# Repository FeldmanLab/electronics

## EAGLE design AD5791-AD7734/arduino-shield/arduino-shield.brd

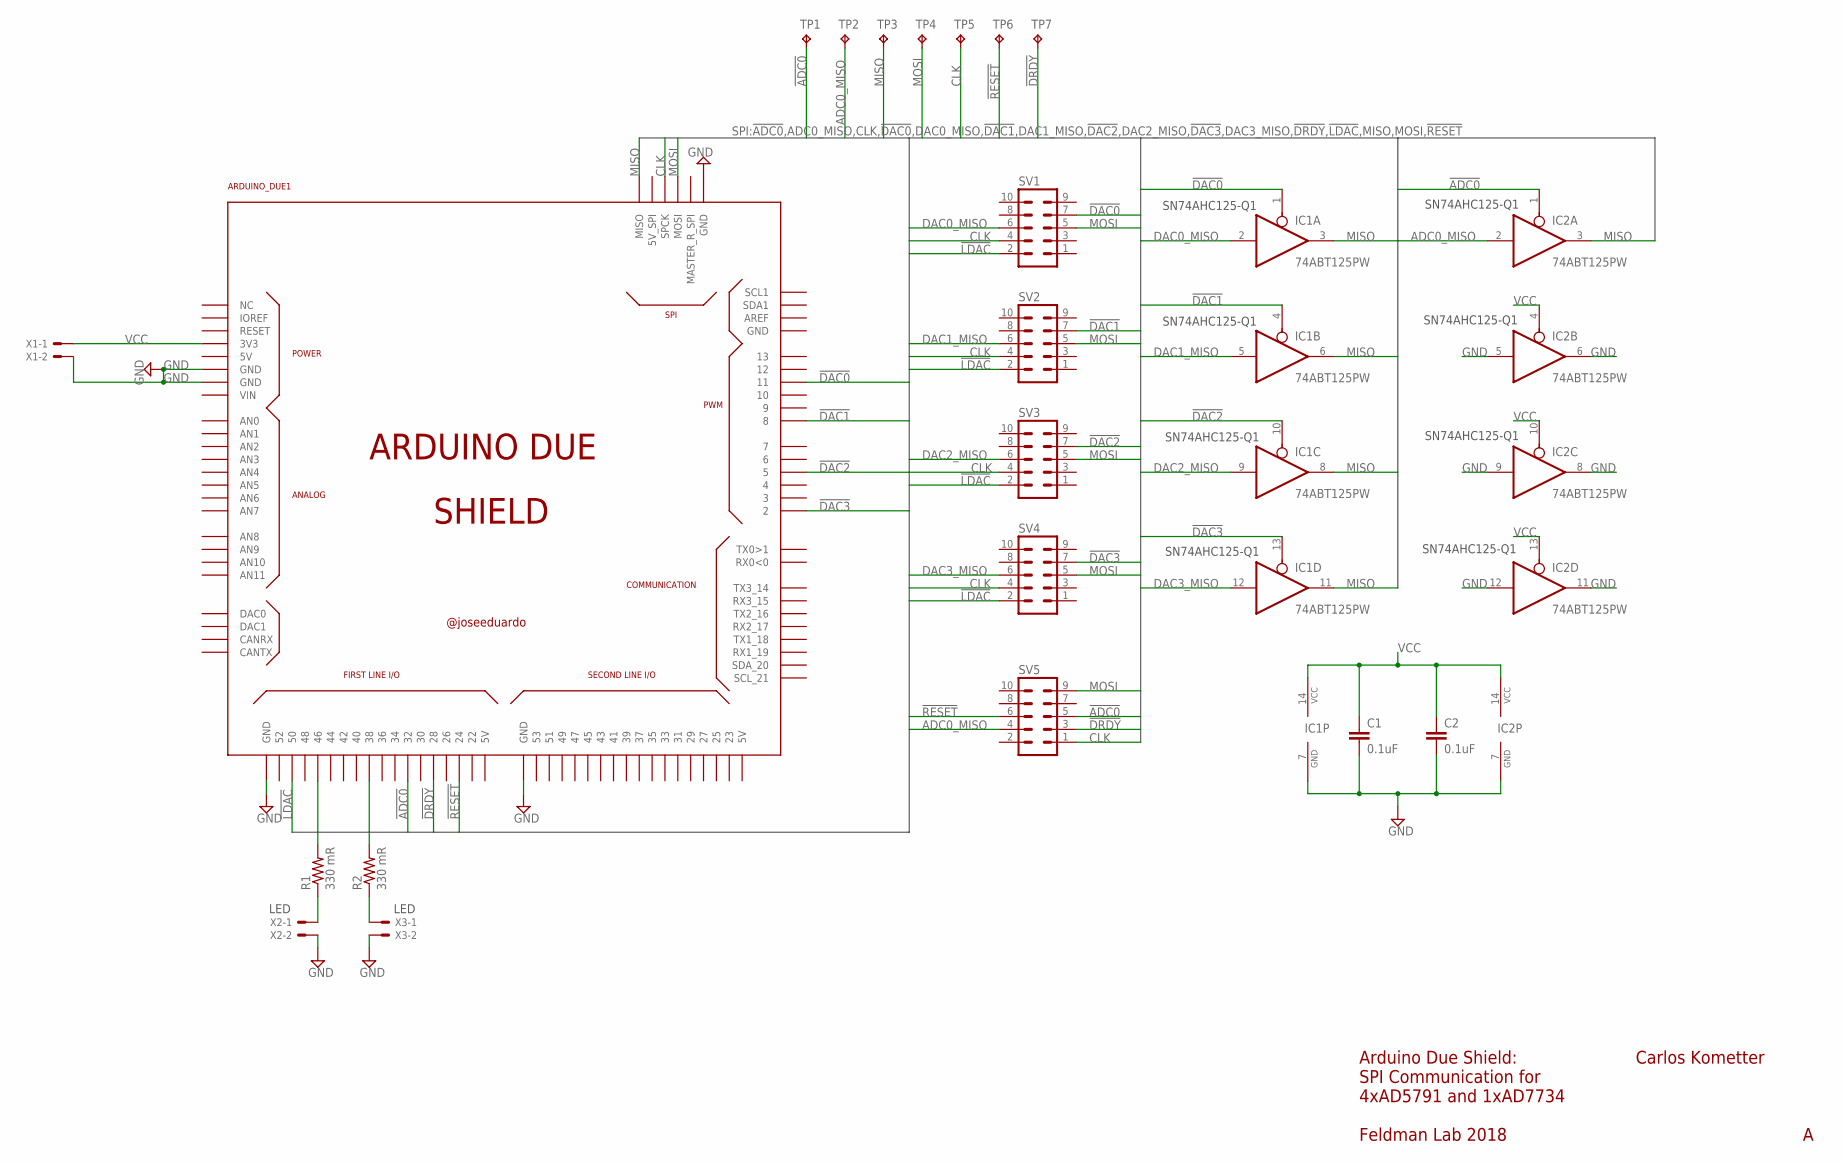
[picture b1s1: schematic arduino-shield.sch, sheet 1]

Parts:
ARDUINO_DUE1: ARDUINO_DUE_SHIELD
C1, C2: 0.1uF; C0603
IC1, IC2: 74ABT125PW; TSSOP14
R1, R2: 330 mR; R1206
SV1, SV2, SV3, SV4, SV5: MA05-2
TP1, TP2, TP3, TP4, TP5, TP6, TP7: TPPAD1-13; P1-13
X1, X2, X3: 22-23-2021

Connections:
!ADC0!: ARDUINO_DUE1.32, IC2.1 (OE), SV5.5, TP1.TP
!DAC0!: ARDUINO_DUE1.11, IC1.1 (OE), SV1.7
!DAC1!: ARDUINO_DUE1.8, IC1.4 (OE), SV2.7
!DAC2!: ARDUINO_DUE1.5, IC1.10 (OE), SV3.7
!DAC3!: ARDUINO_DUE1.2, IC1.13 (OE), SV4.7
!DRDY!: ARDUINO_DUE1.28, SV5.3, TP7.TP
!LDAC!: ARDUINO_DUE1.50, SV1.2, SV2.2, SV3.2, SV4.2
!RESET!: ARDUINO_DUE1.24, SV5.6, TP6.TP
ADC0_MISO: IC2.2 (I), SV5.4, TP2.TP
CLK: ARDUINO_DUE1.SPCK, SV1.4, SV2.4, SV3.4, SV4.4, SV5.1, TP5.TP
DAC0_MISO: IC1.2 (I), SV1.6
DAC1_MISO: IC1.5 (I), SV2.6
DAC2_MISO: IC1.9 (I), SV3.6
DAC3_MISO: IC1.12 (I), SV4.6
GND: ARDUINO_DUE1.GND, ARDUINO_DUE1.GND_1 (GND), ARDUINO_DUE1.GND_2 (GND), ARDUINO_DUE1.GND_3 (GND), ARDUINO_DUE1.GND_5 (GND), C1.2, C2.2, IC1.7 (GND), IC2.5 (I), IC2.6 (O), IC2.7 (GND), IC2.8 (O), IC2.9 (I), IC2.11 (O), IC2.12 (I), X1.2, X2.2, X3.2
MISO: ARDUINO_DUE1.MISO, IC1.3 (O), IC1.6 (O), IC1.8 (O), IC1.11 (O), IC2.3 (O), TP3.TP
MOSI: ARDUINO_DUE1.MOSI, SV1.5, SV2.5, SV3.5, SV4.5, SV5.9, TP4.TP
unnamed: ARDUINO_DUE1.46, R1.2
unnamed: R1.1, X2.1
unnamed: ARDUINO_DUE1.38, R2.2
unnamed: R2.1, X3.1
VCC: ARDUINO_DUE1.3V3, C1.1, C2.1, IC1.14 (VCC), IC2.4 (OE), IC2.10 (OE), IC2.13 (OE), IC2.14 (VCC), X1.1

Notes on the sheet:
Carlos Kometter
Arduino Due Shield: SPI Communication for 4xAD5791 and 1xAD7734 Feldman Lab 2018
LED
SN74AHC125-Q1

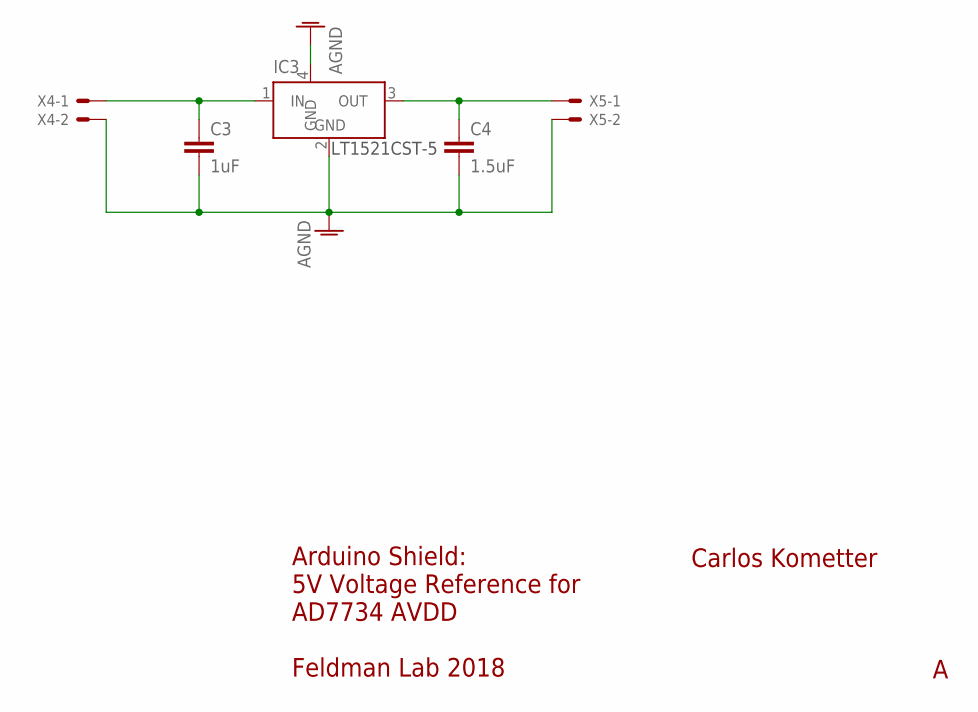
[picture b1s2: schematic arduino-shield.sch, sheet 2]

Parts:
C3: 1uF; C0603
C4: 1.5uF; C0603
IC3: LT1129CST5; SOT223
X4, X5: 22-23-2021

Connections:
AGND: C3.2, C4.2, IC3.2 (GND), IC3.4 (GND), X4.2, X5.2
unnamed: C3.1, IC3.1 (IN), X4.1
unnamed: C4.1, IC3.3 (OUT), X5.1

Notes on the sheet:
Carlos Kometter
Arduino Shield: 5V Voltage Reference for AD7734 AVDD Feldman Lab 2018
LT1521CST-5

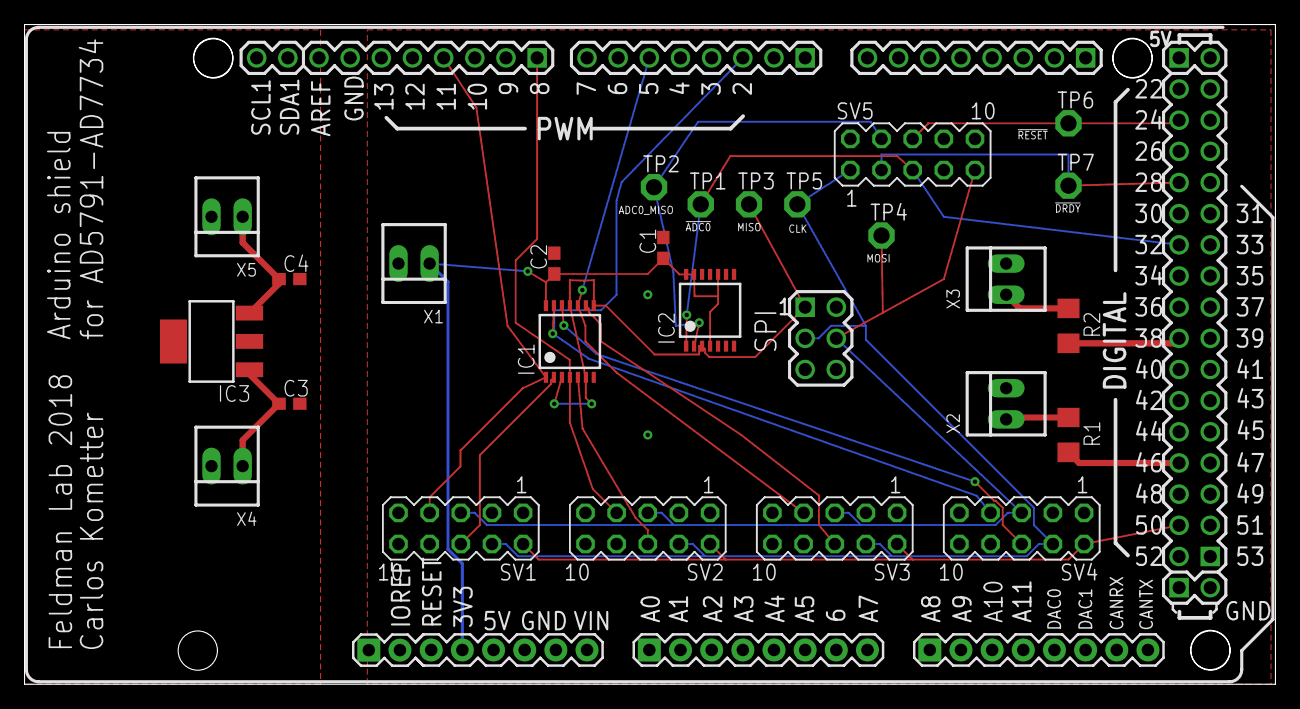
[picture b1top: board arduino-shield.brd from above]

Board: 2 copper layers, 102.0 x 53.8 mm, 27 parts (0 on the bottom side), 25 nets.

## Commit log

2018-11-20 EOL set to LF for text.
2018-11-20 Add arduino-shield for AD5791-AD7734.
2018-11-20 Part numbers renumbered.
2018-11-20 Bill of Materials.`
2018-11-20 Bill of Material update.
2018-11-20 Bill of Materials update.
